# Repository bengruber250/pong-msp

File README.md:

# ELEC 327 S19 
## pong-msp
## Welcome to our MSP430 Pong Github page.
Here you'll find all of our source code, design files, and report files for our little game.
Below are two videos on our project and an excerpt of our report. Enjoy!

## Videos

#### Demonstration
https://www.youtube.com/watch?v=Z2DToJ7af1M

#### Explanation
https://www.youtube.com/embed/VBxOD-HLzUo

## Motivation 
Throughout the semester we've b een exploring the ins and outs of designing and implementing emb edded systems. We've written several drivers for the MSP430's modules and integrated them with software logic to make interesting devices that interact with the real world while meeting tight timing considerations. This semester, the culmination of all of our labs was the Simon project. We put together all of our code from the semester and wrote complicated logic to implement a fun game! This was the source of our motivation to build another game. We enjoyed writing the Simon software and wanted to dive deeper into games running on embedded sy stems. An other driving force was the goal of integrating a graphic display panel into our design. We explored several ideas and finally decided on making a Pong replica.

## System Specification
The Pong game is the arcade classic with two paddles on either end of the screen controlled by users and a ball that is bounced between the paddles and the top and bottom of the screen. If the ball makes it to either end of the screen, a point is scored. The paddles were originally controlled with knobs. Since we wanted to make a close replica of the game we ended up choosing potentiometers for paddle control, a black and white OLED panel (to get a CRT-esque feeling), and a couple of buttons for basic interaction. For software this means that we need ed to implement drivers for GPIO , ADC, and the screen. The game logic required that we implement (but not limit ourselves to) collision checking, bouncing, scoring, ball movement, and detecting the winner of each round.

### Mau (smg10) and Ben (bpg1)

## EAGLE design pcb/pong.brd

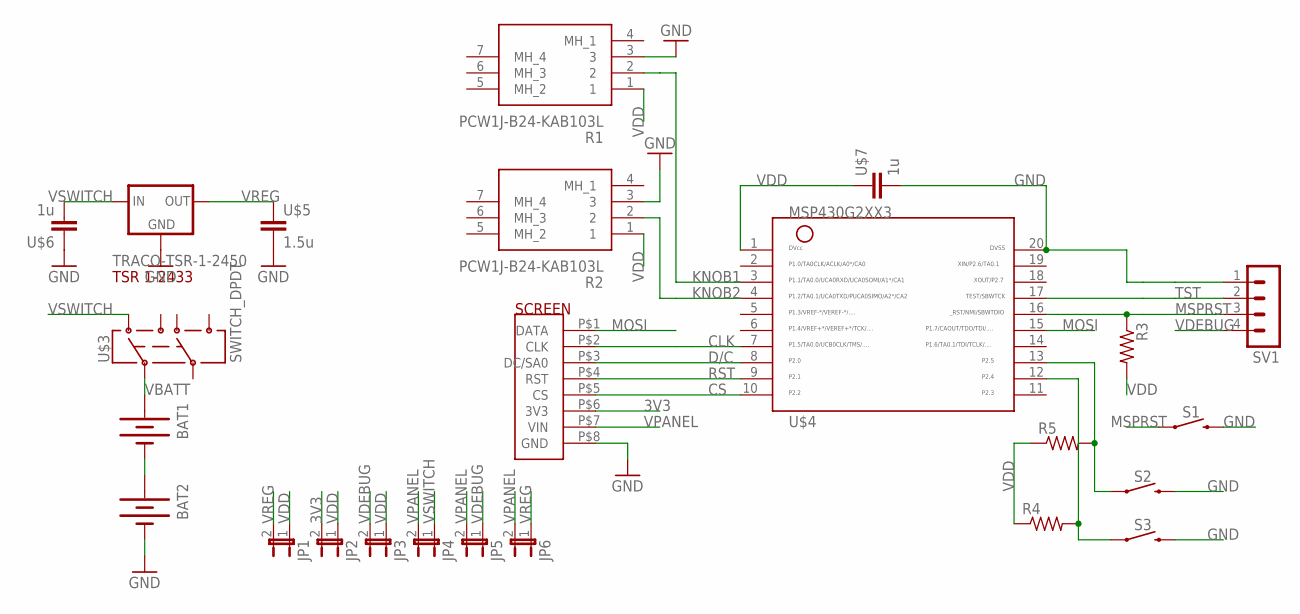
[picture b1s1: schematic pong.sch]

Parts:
BAT1, BAT2: BATTERY; BATTERY_PACK_2AA
JP1, JP2, JP3, JP4, JP5, JP6: JP1E; JP1
R1, R2: PCW1J-B24-KAB103L; PCW1JB24KAB103L
R3, R4, R5: 47k; R0805
S1, S2, S3: MOMENTARY-SWITCH-SPST-PTH-6.0MM; TACTILE_SWITCH_PTH_6.0MM
SV1: 4PINHEAD; MA04-1
U$2: SCREEN_HEADER; SCREEN_FP
U$3: SWITCH_DPDT; JS_DPDT_TH
U$4: MSP430G2XX3TSSOP; PW20
U$5: 1.5u; RESC0805_N
U$6, U$7: 1u; RESC0805_N
U$8: TRACO-TSR-1-2450; SIP3

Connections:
3V3: JP2.2, U$2.P$6 (3V3)
CLK: U$2.P$2 (CLK), U$4.7
CS: U$2.P$5 (CS), U$4.10
D/C: U$2.P$3 (DC/SA0), U$4.8
GND: BAT2.GND (-), R1.3, R2.3, S1.3 (2), S2.3 (2), S3.3 (2), SV1.1, U$2.P$8 (GND), U$4.20, U$5.2, U$6.1, U$7.2, U$8.2 (GND)
KNOB1: R1.2, U$4.3
KNOB2: R2.2, U$4.4
MOSI: U$2.P$1 (DATA), U$4.15
MSPRST: R3.1, S1.1, SV1.3, U$4.16
unnamed: R5.2, S2.1, U$4.13
unnamed: R4.2, S3.1, U$4.12
unnamed: BAT1.GND (-), BAT2.3V (+)
RST: U$2.P$4 (RST), U$4.9
TST: SV1.2, U$4.17
VBATT: BAT1.3V (+), U$3.2
VDD: JP1.1, JP2.1, JP3.1, R1.1, R2.1, R3.2, R4.1, R5.1, U$4.1, U$7.1
VDEBUG: JP3.2, JP5.1, SV1.4
VPANEL: JP4.2, JP5.2, JP6.2, U$2.P$7 (VIN)
VREG: JP1.2, JP6.1, U$5.1, U$8.3 (OUT)
VSWITCH: JP4.1, U$3.1, U$6.2, U$8.1 (IN)

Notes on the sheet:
SCREEN
TSR 1-2433

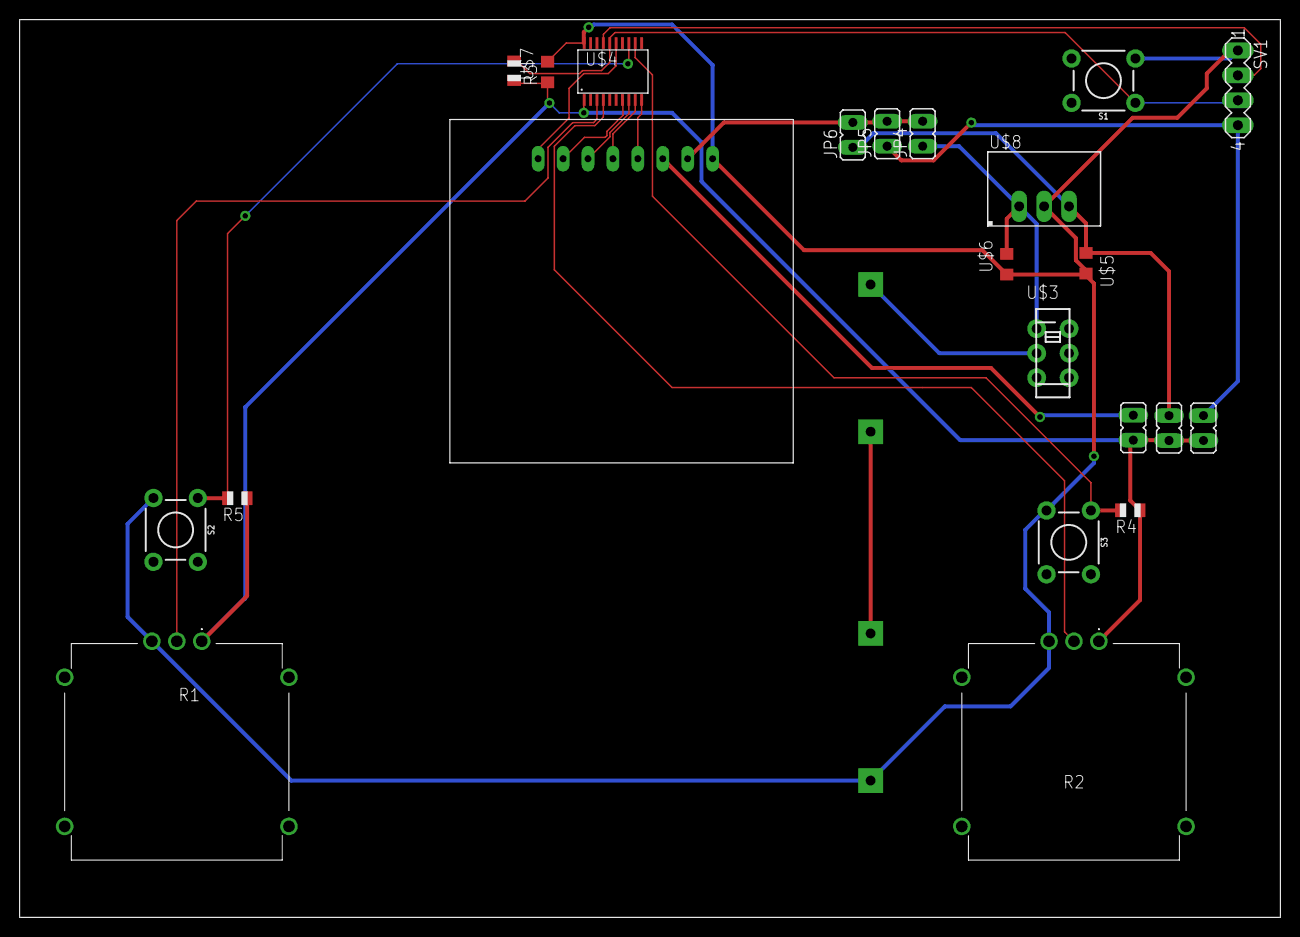
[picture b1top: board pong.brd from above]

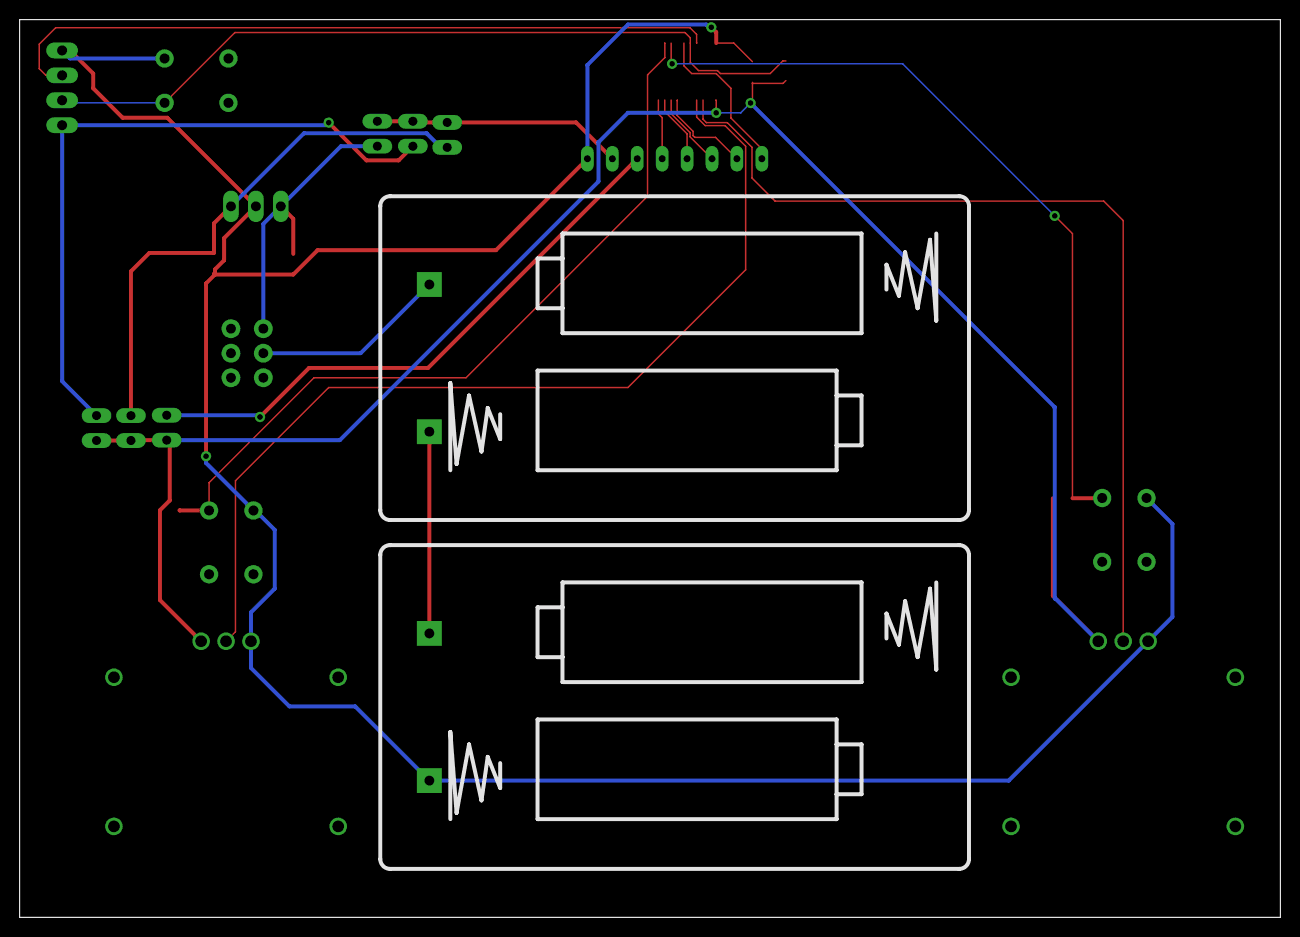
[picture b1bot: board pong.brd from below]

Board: 2 copper layers, 128.5 x 91.5 mm, 24 parts (2 on the bottom side), 20 nets.

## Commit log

2019-04-25 Initial commit.
2019-04-25 Add readme.
2019-04-25 Initialize ccs project for sw development.
2019-04-28 Add software
2019-04-28 Implement draw_rect!
2019-04-28 Maybe fix lib_lcd.
2019-04-29 STOMP BUGS in draw_rect.
2019-04-29 start adc
2019-04-29 gitign
2019-04-29 oops with gitignores
2019-04-29 Template out main.c
2019-04-29 Begin to fill in templates.
2019-04-29 Add extra info regarding init functions.
2019-04-29 Implement rudimentary button code.
2019-04-29 Enable compilation of code.
2019-04-29 Implement display_game_over.
2019-04-29 Implement check_game_over().
2019-04-29 Clean up garbage auto-generated comments.
2019-04-29 Add some stub code for the pong game experience.
2019-04-29 Recalculate capacitance of pongductor.
2019-04-29 Modulate tick epicenter.
2019-04-29 layout stuff
2019-04-29 fix semi colon in pong.h
2019-04-29 ADC single conversion of sequence kinda working
2019-04-29 Make adc sample two channlels. Pot1 is very wrong somehow
2019-04-29 Move pots to c h
2019-04-29 Add code for pots.
2019-04-30 Implement moving paddles.
2019-04-30 Add write_small_string
2019-04-30 Change splash screen string
2019-04-30 Sketch out ball code.
2019-04-30 Update strings.
2019-04-30 Implement bouncing.
2019-04-30 Stop ball paddle clipping
2019-04-30 Update strings and debounce.
2019-04-30 Make ball hang after round.
2019-04-30 Add SW debounce
2019-04-30 Add ball start from prev winner
2019-04-30 Add missing include:
2019-04-30 Add erandom.h and integrate into main
2019-04-30 Add WDT isr to shuffle RNG
2019-04-30 add paddle bounce randomization
2019-04-30 Make rand() inline for faster exec
2019-04-30 Better winning display
2019-04-30 Better debounce
2019-04-30 Prune display libs
2019-04-30 rm unecessary files
2019-04-30 Add comment about source
2019-04-30 Better ball starts
2019-04-30 cleanup comments
2019-05-01 Broaden the paddle hitbox.
2019-05-01 Fix SW debounce
2019-05-01 make paddles reach bottom of screen
2019-05-01 Change order or DTC setup in ADC. Removes all paddle flicker
2019-05-01 fix paddle bottom screen fix
2019-05-01 dumb simple ai
2019-05-01 add more /knobs/ to ai :^)
2019-05-01 Add support for Right and Left btn press
2019-05-01 Add player selection menus
2019-05-01 add better menu strs
2019-05-01 ai done. diff settings need tuning
2019-05-01 fix L/R buttons n move ai diff around
2019-05-01 fix fix buttons
2019-05-01 rm a difficulty level
2019-05-01 fix fix fix buttons
2019-05-01 add report
2019-05-01 good fix good fix
2019-05-01 fixups in report
2019-05-02 Update readme with video links
2019-05-02 fix typos

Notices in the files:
parts and their libraries:
SparkFun-Switches: Licensing: Creative Commons ShareAlike 4.0 International - https://creativecommons.org/licenses/by-sa/4.0
